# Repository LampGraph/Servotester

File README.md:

# Servotester
Сервотестер на Atmega8l.

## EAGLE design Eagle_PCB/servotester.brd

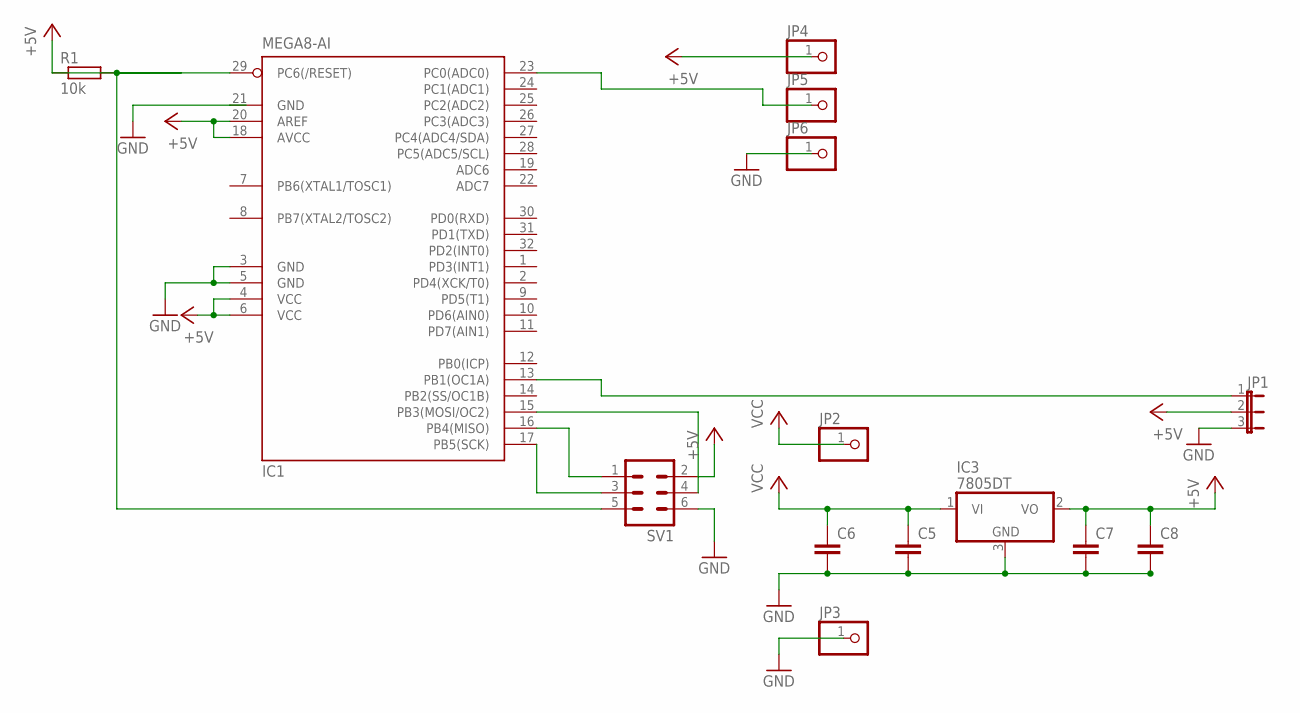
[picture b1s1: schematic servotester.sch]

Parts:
C5, C7: C-EUC1608; C1608
C6, C8: C-EUC3216; C3216
IC1: MEGA8-AI; TQFP32-08
IC3: 7805DT; TO252
JP1: JP2E; JP2
JP2, JP3, JP4, JP5, JP6: PINHD-1X1; 1X01
R1: 10k; R0603
SV1: MA03-2

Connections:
+5V: C7.1, C8.1, IC1.4 (VCC), IC1.6 (VCC), IC1.18 (AVCC), IC1.20 (AREF), IC3.2 (VO), JP1.2, JP4.1, R1.1, SV1.2
GND: C5.2, C6.2, C7.2, C8.2, IC1.3 (GND), IC1.5 (GND), IC1.21 (GND), IC3.3 (GND), JP1.3, JP3.1, JP6.1, SV1.6
unnamed: IC1.29 (PC6(/RESET)), R1.2, SV1.5
unnamed: IC1.23 (PC0(ADC0)), JP5.1
unnamed: IC1.13 (PB1(OC1A)), JP1.1
unnamed: IC1.16 (PB4(MISO)), SV1.1
unnamed: IC1.17 (PB5(SCK)), SV1.3
unnamed: IC1.15 (PB3(MOSI/OC2)), SV1.4
VCC: C5.1, C6.1, IC3.1 (VI), JP2.1

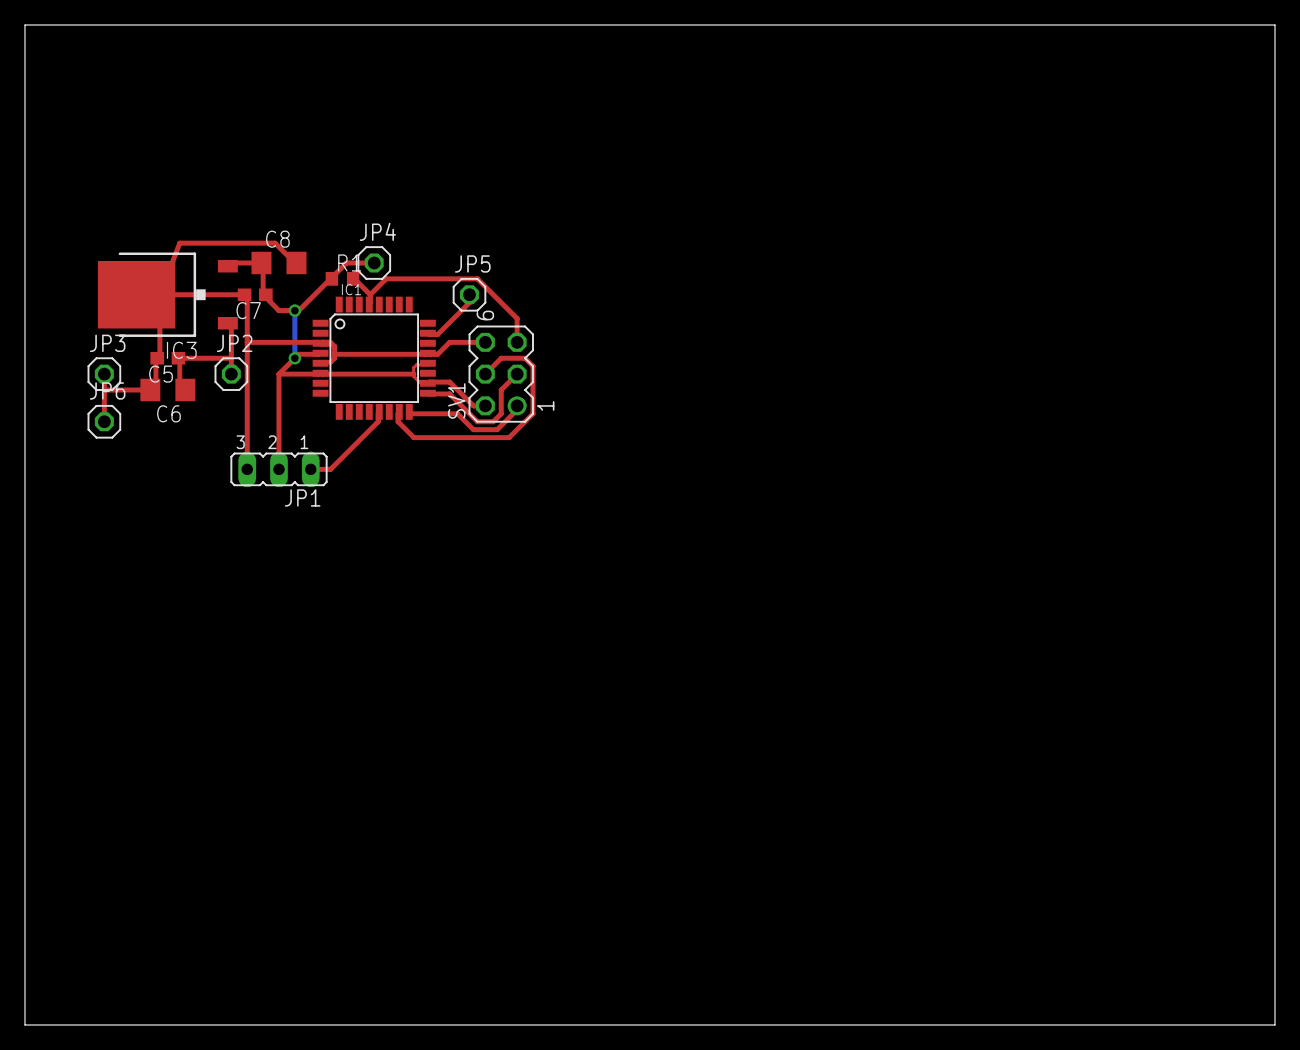
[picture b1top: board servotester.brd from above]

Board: 2 copper layers, 100.0 x 80.0 mm, 14 parts (0 on the bottom side), 9 nets.

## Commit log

2016-05-19 initial project version
2016-05-22 modified: Servotester.atsuo modified: Servotester/Debug/Servotester.elf modified: Servotester/Debug/Servotester.hex modified: Servotester/Debug/Servotester.lss modified: Servotester/Debug/Servotester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
2016-05-22 deleted: README.md deleted: github deleted: github.pub deleted: id_rssa deleted: id_rssa.pub deleted: lag deleted: lag.pub deleted: rsa1 deleted: rsa1.pub
2016-05-24 modified: README.md modified: Servotester/Debug/Makefile modified: Servotester/Debug/Servotester.d modified: Servotester/Debug/Servotester.elf modified: Servotester/Debug/Servotester.hex modified: Se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
2016-05-25 Update Servotester.cpp
    Add a comments
2016-05-25 Changes to be committed: new file: Eagle PDB/eagle.epf new file: Eagle PDB/servotester.b#1 new file: Eagle PDB/servotester.b#2 new file: Eagle PDB/servotester.b#3 new file: Eagle PDB/servotester.brd 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
2016-05-25 Changes to be committed: renamed: Eagle PDB/eagle.epf -> Eagle_PCB/eagle.epf renamed: Eagle PDB/servotester.b#1 -> Eagle_PCB/servotester.b#1 renamed: Eagle PDB/servotester.b#2 -> Eagle_PCB/servoteste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
2016-05-25 Changes to be committed: new file: Eagle_PCB/PCB.png new file: "Eagle_PCB/\320\241\321\205\320\265\320\274\320\260.png"
2016-05-25 Changes to be committed: renamed: "Eagle_PCB/\320\241\321\205\320\265\320\274\320\260.png" -> Eagle_PCB/Scheme.png
